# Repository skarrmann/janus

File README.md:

# Janus Keyboard

Janus is a small 34 key split ortholinear keyboard, powered by two Seeed XIAO RP2040 with the keyboards halves connected by an ethernet cable.

The PCB works as both a logical PCB and a bottom plate.

This keyboard is a grid of 1U keys with no special features: no hotswap, no RGB (except those on the XIAO RP2040), no OLED screen, no knobs. It only supports Cherry MX style switches.

## Project structure

* [`gerbers`](gerbers): Gerber files for PCB manufacturing
* [`graphics`](graphics): Source assets for PCB silkscreen
* [`kicad`](kicad): KiCad project files (schematics and PCB designs)
* [`kicad-libraries`](kicad-libraries): KiCad components and footprints
* [`images`](images): Images for project documentation
* [`firmware`](firmware): Firmware files

## PCBs

There is only one PCB design, and 4 copies of this PCB are used to assemble a single keyboard with bottom plates.

The PCB serves as both halves of the split keyboard, as well as bottom plates for those halves.

Flip the board horizontally to get the other keyboard half.

Both keyboard halves have surface-mount solder pads for diodes, microcontroller, and ethernet jack, all on the top side of the PCB.

The PCB is flipped vertically to serve as a bottom plate. The bottom plates are screwed directly to the logical PCB. Note the cutouts on the PCB line up with all the components' through-hole and plastic pins sticking out the bottom of the logical PCB.

The two halves of the keyboard communicate using full-duplex serial. Note the RX and TX connections are flipped on the top/bottom ethernet jack connections (TX connects to RX and vice-versa).

## Keyboard firmware

* KMK
    * Setup instructions and basic configuration is in this repo: [`firmware/kmk`](firmware/kmk)
* [QMK](https://github.com/qmk/qmk_firmware/tree/master/keyboards/janus)

## Bill of materials

Part | Purpose | Quantity | Notes
---- | ------- | -------- | ---------
PCB  | circuit board | 4 |
Seeed XIAO RP2040 | Microcontroller board | 2 |
Kycon GMX-SMT2-N-88 | connect keyboard halves | 2 | This **exact** connector must be used to fit the board footprint!
1N4148 SOD-123 | Diodes for keyboard row-column matrix | 34 |
Keyswitches |  | 34 | PCB mount (5 pin) switches recommended
Keycaps |  | 34 |
M2 6mm screws | Secure main PCB and plate PCBs | 8 |
M2 nuts | Secure main PCB and plate PCBs | 8 |
2mm tall rubber bumpons | Raise board above desk surface and provide skid resitance | 12 |

You will also need an ethernet patch cable to connect the keyboard halves. Monoprice Micro SlimRun cables are my personal recommendation.

## PCB manufacturing settings

These are the manufacturing settings I used when ordering from JLCPCB:

* **Base Material**: FR4
* **Layers**: 2
* **Dimensions**: (whatever the gerber file specifies)
* **PCB Qty**: 5
* **Different Design**: 1
* **Delivery Format**: Single PCB
* **PCB Thickness**: 1.6
* **PCB Color**: Black
* **Silkscreen**: White
* **Surface Finish**: LeadFree HASL-RoHS
* **Outer Copper Weight**: 1 oz
* **Gold Fingers**: No
* **Confirm Production File**: No
* **Flying Probe Test**: Fully Test
* **Castellated Holes**: No
* **Remove Order Number**: Specify a location

**IMPORTANT:** The PCBs has ["JLCJLCJLCJLC" silkscreen text](https://support.jlcpcb.com/article/28-how-to-remove-order-number-from-your-pcb) underneath the ethernet jack footprint. If you want to remove the order number from the boards or you want to print the PCBs with another manufacturer, then I recommend removing this silkscreen text from the `.kicad_pcb` file, and then regenerate the gerber files.

## Design decisions

The PCB design is in favor of PCB manufacturers' minimum order quantity of 5 and cheaper price at board sizes 100mm x 100mm. Since 4 PCBs are required to build the board with bottom plates, you are only left with one spare PCB.

The Seeed XIAO RP2040 was chosen as the microcontroller because its size works well with the intended layout. It just barely fits within the space of an MX keyswitch. The castellated pads permit surface-mount soldering, which makes the reversible PCB design more practical.

An ethernet connector was chosen to connect the keyboard halves because its connector fits within the space of an MX keyswitch. The Kycon GMX-SMT2-N-88 part was the best fit I could find for this use case. Although only 4 wires are needed for full-duplex serial communication between halves, an 8P8C ethernet jack was chosen over other modular jacks due to better part availability.

## Build tips

* Before starting, check if the PCBs are warped, and bend them to be perfectly flat before soldering.
* Solder the top SMD components first, in order of smallest to largest: diodes, XIAO RP2040, 8P8C ethernet jack
* Before soldering the XIAO RP2040, adhere a piece of electrical tape to its back to prevent potential shorts
    * 
* Use a piece of heat-resistant tape to align the XIAO RP2040 in place when soldering. Solder the opposing edge pads, and ensure the component is straight and flat.
    * 
* Solder the switches last!
    * 
* Attaching the bottom plates with M2 screws and nuts takes patience and a steady hand. If it's too annoying, use double-sided tape instead!

## KiCad project notes

Separate symbols and footprints are defined for the bottom plate cutouts (both for for MX switches and the 8P8C ethernet jack). No special code nor plugins are used here; these cutouts are manually positioned in the PCB design.

## Revision history

* **Janus 1.0** (2022-06-24)
    * Initial PCB design

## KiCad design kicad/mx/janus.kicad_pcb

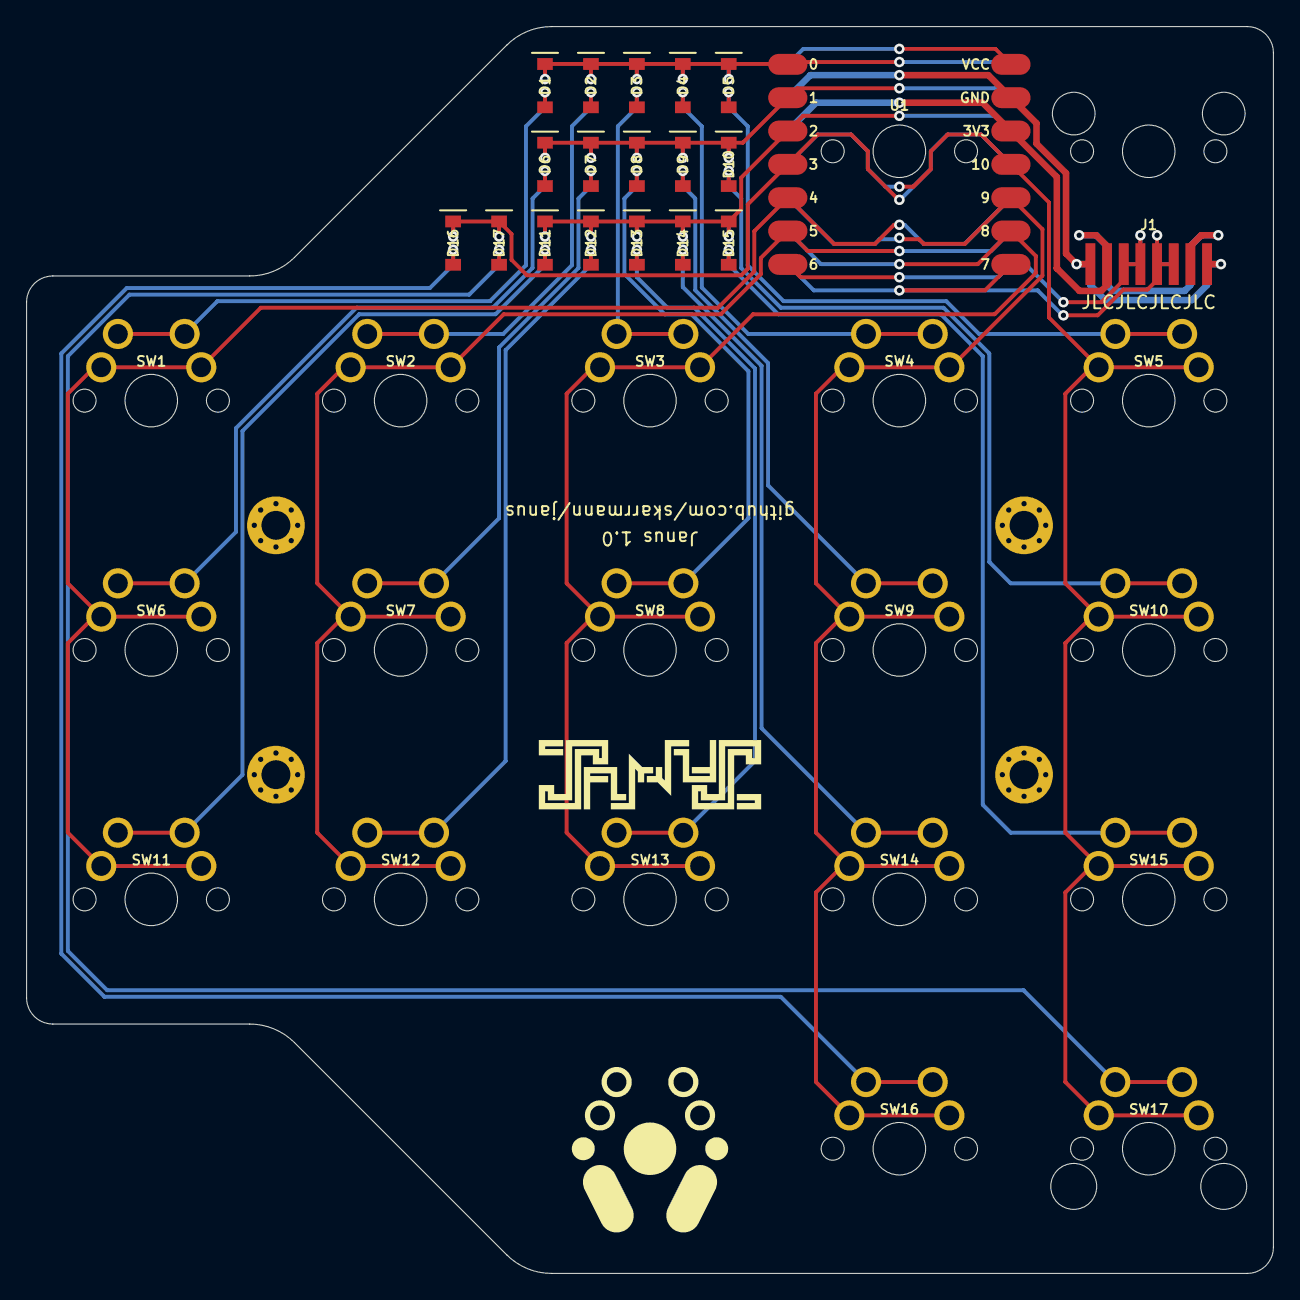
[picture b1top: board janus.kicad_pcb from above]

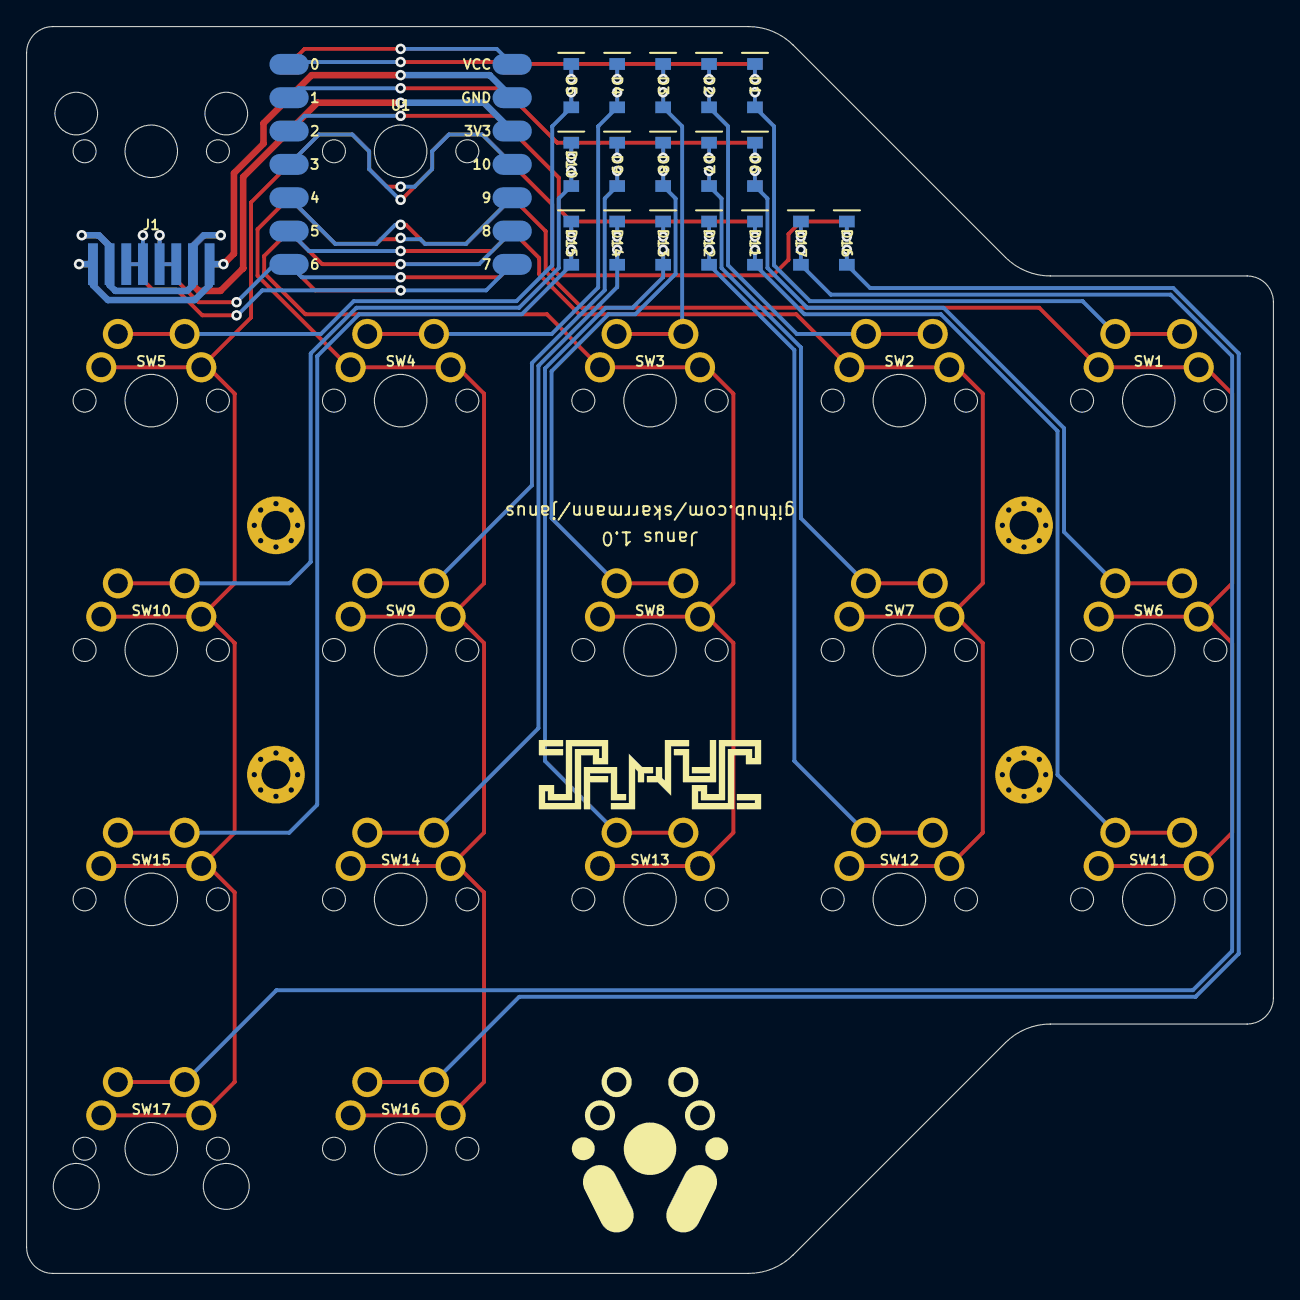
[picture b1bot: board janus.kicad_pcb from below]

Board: 2 copper layers, 95.0 x 95.0 mm, 62 parts (2 on the bottom side), 30 nets.

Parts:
CUTOUT1, CUTOUT2: Cutout-MX_Full; Cutout_SW_MX_Full
CUTOUT3, CUTOUT4, CUTOUT5, CUTOUT6, CUTOUT7, CUTOUT8, CUTOUT9, CUTOUT10, CUTOUT11, CUTOUT12, CUTOUT13, CUTOUT15, CUTOUT16, CUTOUT17: Cutout-MX; Cutout_SW_MX_Pads
CUTOUT14: Cutout; Cutout_SW_MX_Pads
CUTOUT18: Cutout-8P8C; Cutout_8P8C_SMT
D1, D2, D3, D4, D5, D6, D7, D8, D9, D10, D11, D12, D13, D14, D15, D16, D17: D; D_SOD-123_Reversible
H1, H2, H3, H4: Hole_Pad; Mount_M2
J1: 8P8C Double Sided; 8P8C_SMT_Double_Sided
LOGO1: Logo-Bottom; Logo_Janus
LOGO2: Logo-Top; Logo_Janus
LOGO3: Footprint-Top; Logo_Janus_Footprint
LOGO4: Footprint-Bottom; Logo_Janus_Footprint
SW1, SW2, SW3, SW4, SW5, SW6, SW7, SW8, SW9, SW10, SW11, SW12, SW13, SW14, SW15, SW16, SW17: SW_Push; SW_MX_Reversible
U1: XIAO RP2040; XIAO-RP2040_Reversible

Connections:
COL1: SW1.1, SW6.1, SW11.1, U1.5 (4)
COL2: SW2.1, SW7.1, SW12.1, U1.6 (5)
COL3: SW3.1, SW8.1, SW13.1, U1.9 (8)
COL4: SW4.1, SW9.1, SW14.1, SW16.1, U1.10 (9)
COL5: SW5.1, SW10.1, SW15.1, SW17.1, U1.11 (10)
GND: J1.1, J1.8, J1.9, J1.16, U1.13 (GND)
unnamed: D1.2 (A), SW1.2
unnamed: D2.2 (A), SW2.2
unnamed: D3.2 (A), SW3.2
unnamed: D4.2 (A), SW4.2
unnamed: D5.2 (A), SW5.2
unnamed: D6.2 (A), SW6.2
unnamed: D7.2 (A), SW7.2
unnamed: D8.2 (A), SW8.2
unnamed: D9.2 (A), SW9.2
unnamed: D10.2 (A), SW10.2
unnamed: D11.2 (A), SW11.2
unnamed: D12.2 (A), SW12.2
unnamed: D13.2 (A), SW13.2
unnamed: D14.2 (A), SW14.2
unnamed: D15.2 (A), SW15.2
unnamed: D16.2 (A), SW16.2
unnamed: D17.2 (A), SW17.2
ROW1: D1.1 (K), D2.1 (K), D3.1 (K), D4.1 (K), D5.1 (K), U1.1 (0)
ROW2: D6.1 (K), D7.1 (K), D8.1 (K), D9.1 (K), D10.1 (K), U1.2 (1)
ROW3: D11.1 (K), D12.1 (K), D13.1 (K), D14.1 (K), D15.1 (K), U1.3 (2)
ROW4: D16.1 (K), D17.1 (K), U1.4 (3)
RX: J1.3, J1.4, J1.13, J1.14, U1.8 (7)
TX: J1.5, J1.6, J1.11, J1.12, U1.7 (6)
VCC: J1.2, J1.7, J1.10, J1.15, U1.12 (3V3)

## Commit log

2022-06-25 Center silkscreen logo
2022-06-25 Update keyswitch and keycaps vendor URLs
2022-07-15 Add project photos
2022-07-15 Fix readme grammar and typos
2022-07-15 Add KMK firmware code and instructions
2022-07-15 Fix wording mistake in build tip
2022-07-17 Update KMK firmware with proper board definition and usable layout
2022-07-20 Update KMK firmware implementation with custom oneshot mod module
2022-07-20 Fix typo in firmware readme
2022-07-20 Fix typo in oneshot mod module
2022-07-20 Clean up file formatting
2022-07-22 Update BOM vendor links
2022-09-14 Adjust locking key positions in KMK firmware
2022-09-15 Note QMK pull request submitted
2022-09-16 Simplify KMK custom oneshot implementation
2022-09-24 Link to QMK firmware
2022-09-26 Further refine KMK custom oneshot key implementation
2023-11-02 Remove vendor URLs
2023-11-23 Update KMK firmware and custom oneshot implementation
2023-11-23 Update KMK firmware readme links
2025-08-09 Update KMK firmware
2025-08-09 Remove left shift as oneshot ignore key
